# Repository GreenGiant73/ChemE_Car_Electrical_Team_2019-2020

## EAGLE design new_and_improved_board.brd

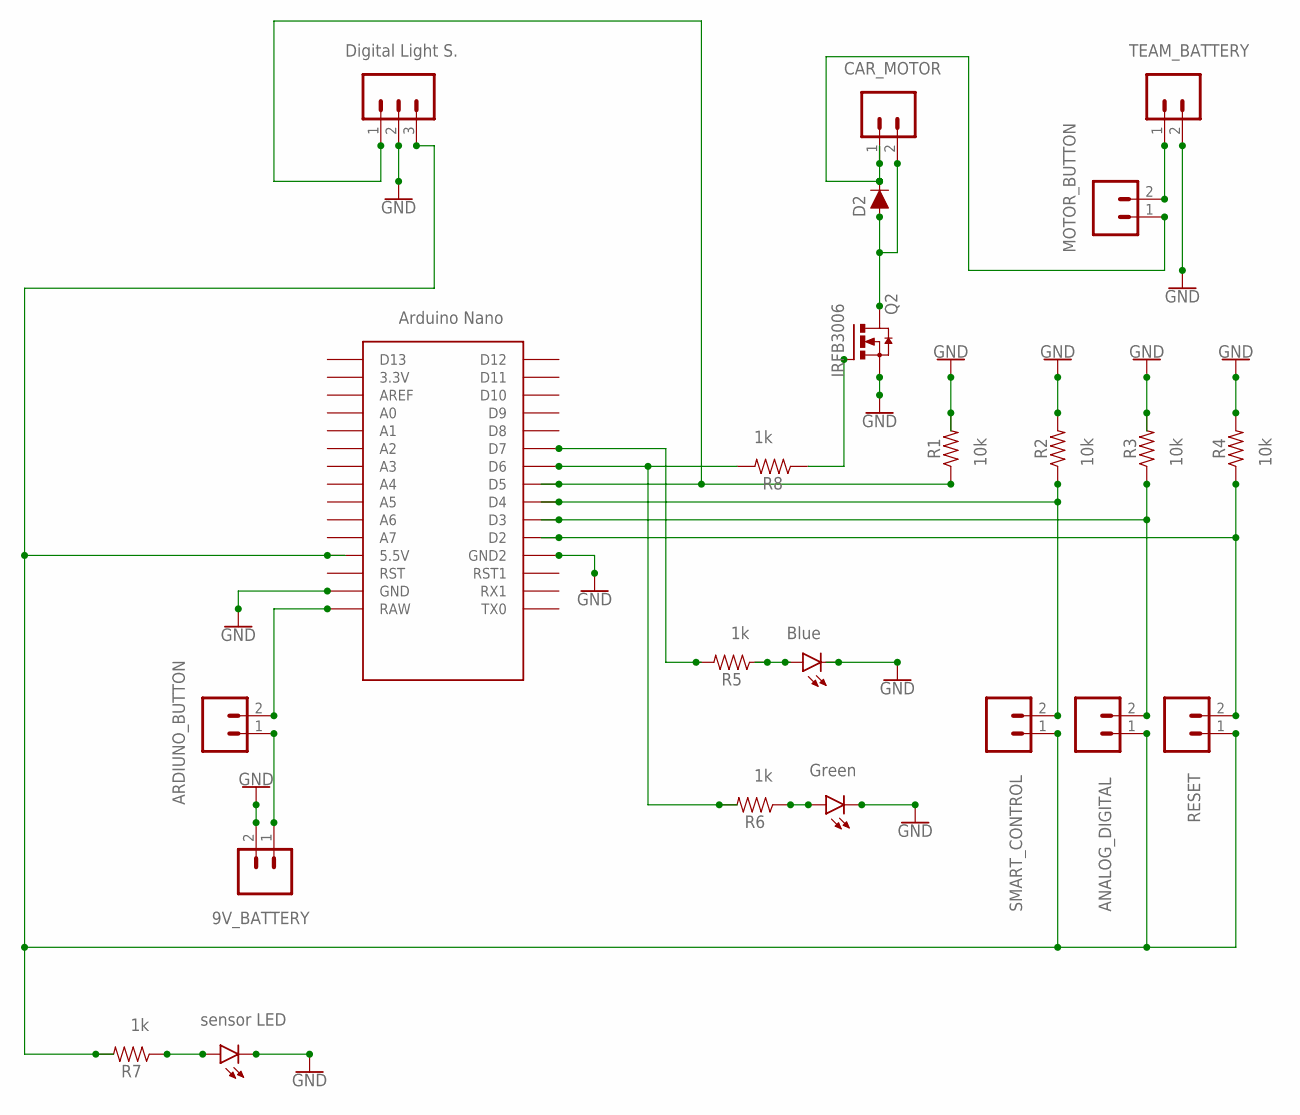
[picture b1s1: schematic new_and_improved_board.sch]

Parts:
D2: 200mA/100V/1V; DIODE-1N4148
D4, D5, D6: LED3MM; LED_3MM
J1, J2, J3: CONN_02; 1X02
J4: 455-1750-1-ND; 1X03
Q2: IRF3704L-V; TO262-V
R1, R2, R3, R4, R5, R6, R7, R8: 1M; AXIAL-0.3
S1, S2, S3, S4, S5: CONN_02; 1X02
U$1: NANO

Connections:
5V: J4.3, R7.P$2 (2), S2.1, S4.1, S5.1, U$1.5V (5.5V)
9V: S1.2, U$1.RAW
9VBAT: J2.1, S1.1
GND: D4.K (C), D5.K (C), D6.K (C), J2.2, J3.2, J4.2, Q2.3 (S), R1.P$2 (2), R2.P$2 (2), R3.P$2 (2), R4.P$2 (2), U$1.GND, U$1.GND1 (GND2)
unnamed: R6.P$2 (2), R8.P$2 (2), U$1.D6
unnamed: D2.A, J1.2, Q2.2 (D)
unnamed: Q2.1 (G), R8.P$1 (1)
unnamed: J4.1, R1.P$1 (1), U$1.D5
unnamed: R2.P$1 (1), S2.2, U$1.D4
unnamed: R3.P$1 (1), S4.2, U$1.D3
unnamed: R4.P$1 (1), S5.2, U$1.D2
unnamed: R5.P$2 (2), U$1.D7
unnamed: D4.A, R5.P$1 (1)
unnamed: D5.A, R6.P$1 (1)
unnamed: D2.C, J1.1, S3.1
unnamed: J3.1, S3.2
unnamed: D6.A, R7.P$1 (1)

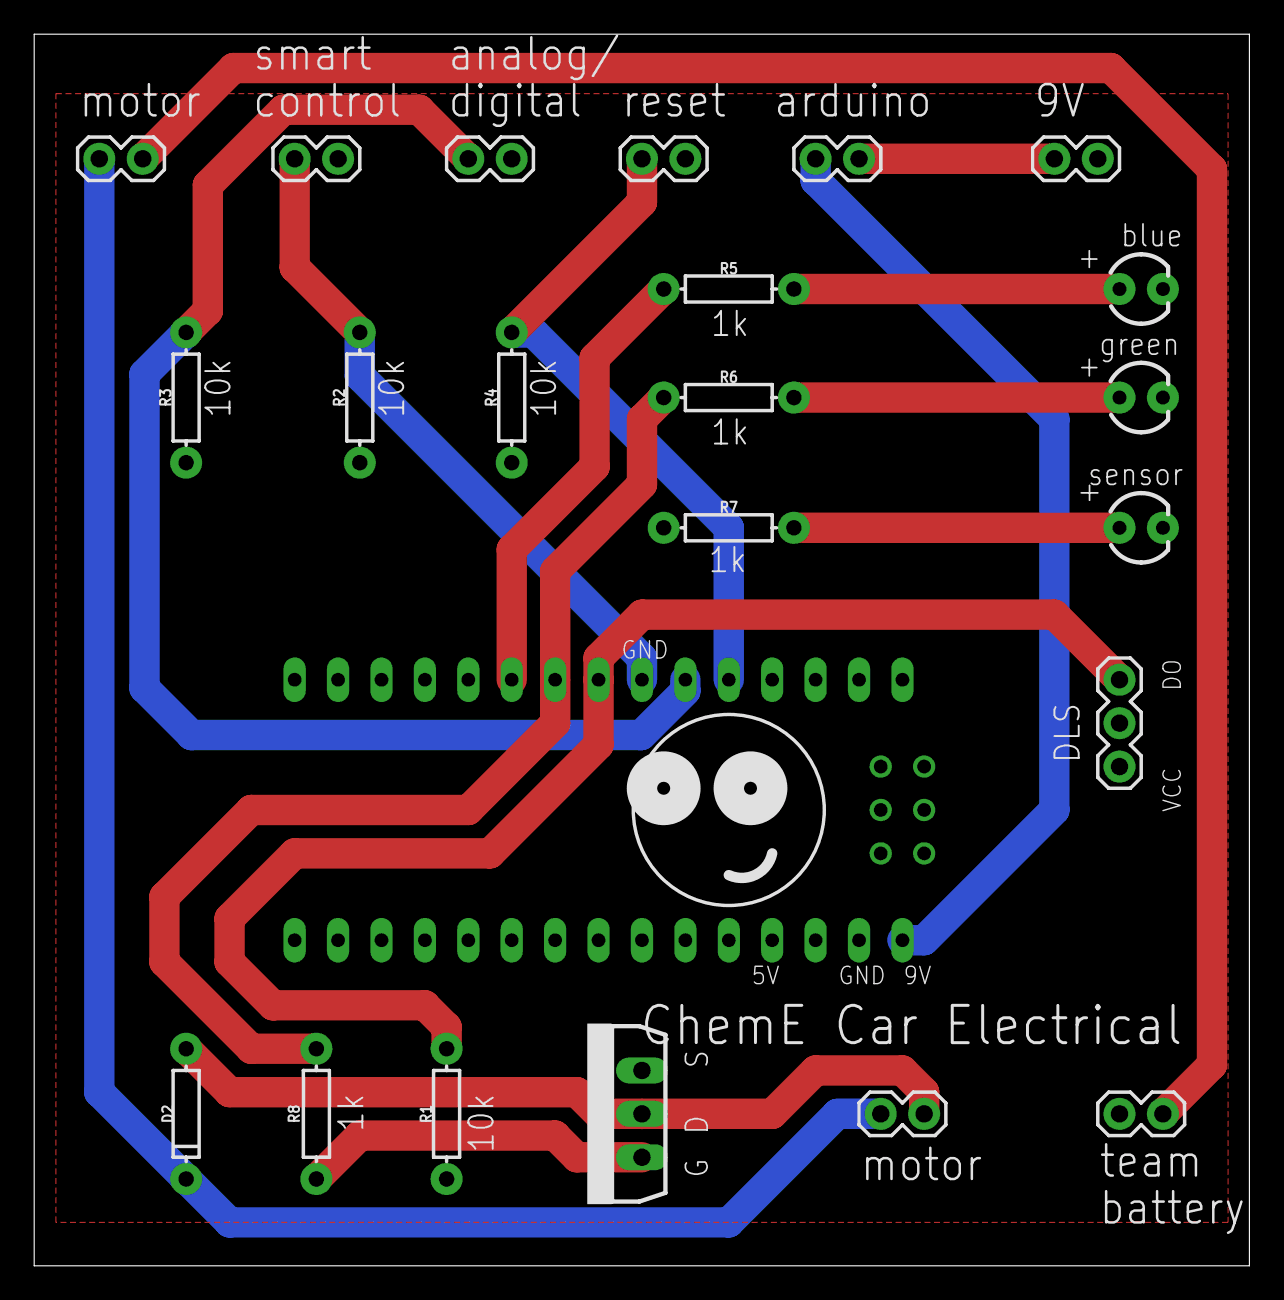
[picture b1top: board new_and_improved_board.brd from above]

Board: 2 copper layers, 71.1 x 72.1 mm, 23 parts (0 on the bottom side), 17 nets.

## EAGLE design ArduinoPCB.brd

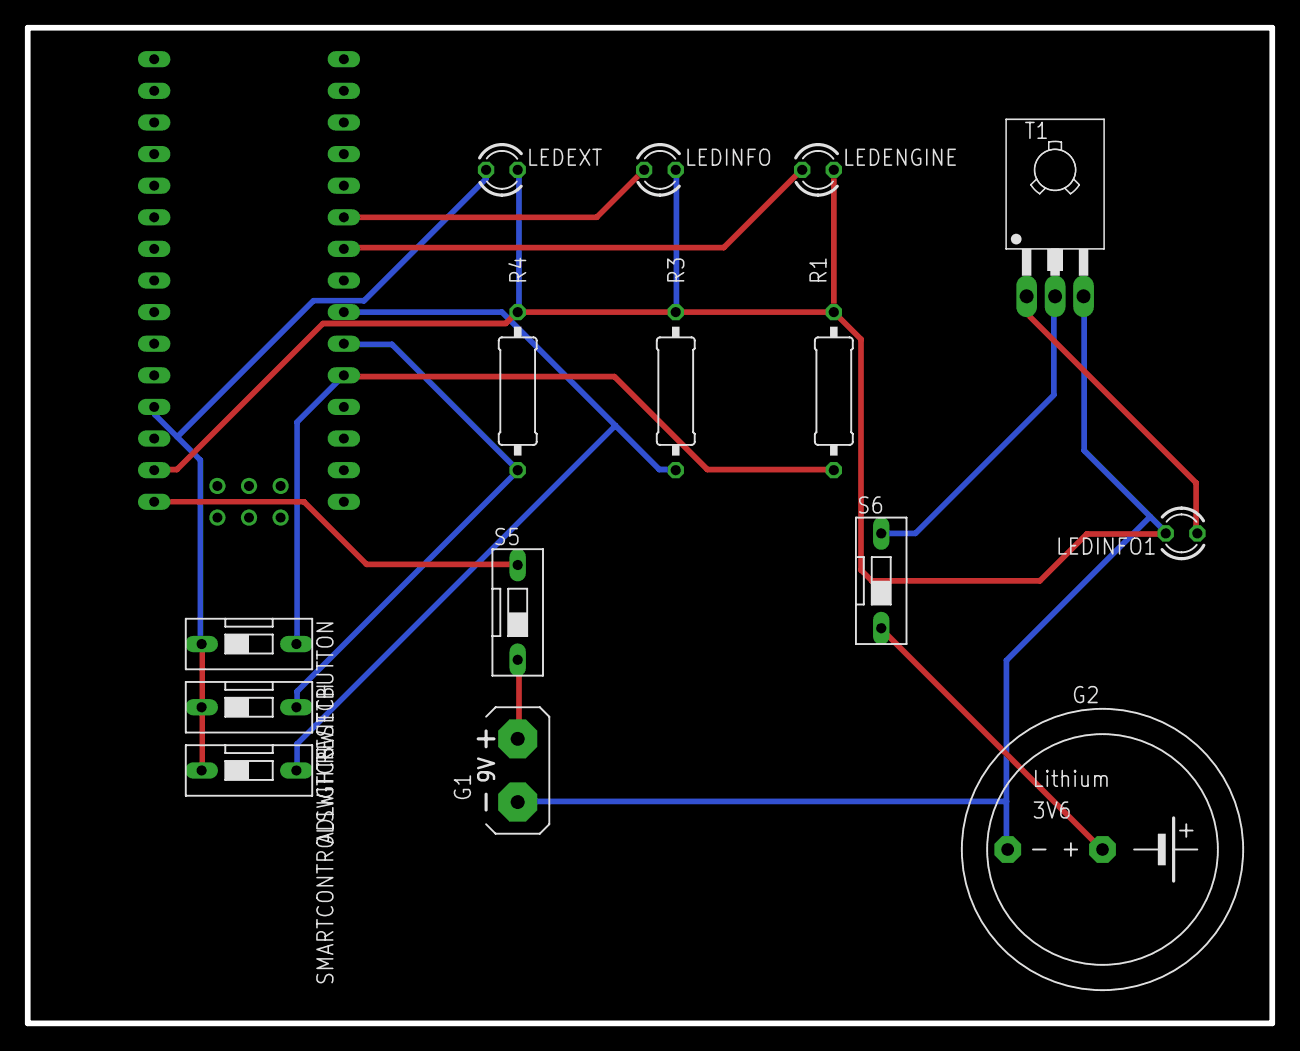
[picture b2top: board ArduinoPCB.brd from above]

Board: 2 copper layers, 100.0 x 80.0 mm, 17 parts (0 on the bottom side), 12 nets.

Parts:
ADLIGHTSWITCH: DS-01
FRAME1: FRAME-LETTER; CREATIVE_COMMONS
G1: AB9V
G2: SL-340/P3.6V
LEDENGINE: LED3MM
LEDEXT: LED3MM
LEDINFO, LEDINFO1: LED3MM
R1, R3, R4: 0309/12
RESETBUTTON: DS-01
S5, S6: DS-01
SMARTCONTROLSWITCH: DS-01
T1: 2N4923; TO126
U$1: NANO

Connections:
unnamed: ADLIGHTSWITCH.2, R4.1, U$1.D3
unnamed: R3.1, SMARTCONTROLSWITCH.2, U$1.D4
unnamed: G2.+, S6.1
unnamed: G1.+, S5.1
unnamed: LEDINFO1.A, T1.1
unnamed: G1.-, G2.-, LEDENGINE.K, LEDEXT.K, LEDINFO.K, LEDINFO1.K, R1.2, R3.2, R4.2, T1.3, U$1.GND
unnamed: ADLIGHTSWITCH.1, LEDEXT.A, RESETBUTTON.1, SMARTCONTROLSWITCH.1, U$1.5V
unnamed: LEDENGINE.A, U$1.D6
unnamed: LEDINFO.A, U$1.D7
unnamed: S5.2, U$1.RAW
unnamed: R1.1, RESETBUTTON.2, U$1.D2
unnamed: S6.2, T1.2

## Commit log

2019-05-21 test
2019-08-20 Updated Electrical Box Details file
2019-09-15 Added list of materials
2019-09-27 Updated Weekly Readings
2019-10-25 PCB Design
2019-10-25 added pcb
2019-10-26 box design
2019-11-02 Updated PCB schematic
2019-11-02 Fritzing Schematic
2019-11-09 Updated Board
2019-11-09 updated PCB
2020-01-02 added through holes for motor connection and through holes for sensor connection. also changed PCB layout.
2020-01-02 Added New Schematic
2020-01-04 new schematic modeling the shield layout
2020-01-04 modifications made to ArduinoPCB_test
2020-01-05 added analog/digital switch
2020-01-05 routing PCB layout
2020-01-06 finished labeling signals and buttons
2020-01-07 switched out switches for through-holes
2020-01-07 added team name
2020-01-07 resize board
2020-01-25 thicker wire lines
2020-01-25 single square
2020-01-25 thicker lines
2020-01-28 added ground and power planes, and changed resistor values/added resistor after the mosfet gate
2020-01-31 added æsthetically pleasing features
2020-01-31 box design with embedded images
2020-01-31 new Box 2 folder
2020-02-06 resdimensioning the circuit box
2020-02-09 new box
2020-02-09 finalizing box design
2020-02-09 making images into vector art for vector image
2020-02-10 vectorized rest of images, changes logo on back, added bear line art, and changed line weight to 0.072pt
2020-02-14 design changes
2020-03-06 new box design
2020-03-07 poster

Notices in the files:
parts and their libraries:
SparkFun-Aesthetics: Licensing: Creative Commons ShareAlike 4.0 International - https://creativecommons.org/licenses/by-sa/4.0
SparkFun-Aesthetics: Released under the Creative Commons Attribution Share-Alike 4.0 License
SparkFun-Aesthetics: https://creativecommons.org/licenses/by-sa/4.0
